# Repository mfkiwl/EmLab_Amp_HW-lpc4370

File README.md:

# EmLab Amp HW
Hardware for 80dB amp + digitizer

## Notes
- the TPS65131 regulator does some weird stuff - maybe exchange for similar AD part?

## TODO
- debug prototype

### Schematic
- nothing

### PCB
- nothing

## Links
- [BOM](https://octopart.com/bom-tool/Xo4yGKYB)
- [LPC Link 2 Schematic](https://www.nxp.com/downloads/en/schematics/LPC-Link2-SCH.pdf)
- [BGA PCB Guidelines](https://www.nxp.com/docs/en/application-note/AN10778.pdf)
- [Proper grounding #1](https://www.analog.com/en/analog-dialogue/articles/staying-well-grounded.html)
- [Proper grounding #2](https://www.maximintegrated.com/en/app-notes/index.mvp/id/5450)
- [LPC4370 Datasheet](https://www.nxp.com/docs/en/data-sheet/LPC4370.pdf)
- [W25Q80BVSSIG Datasheet](https://openwrt.org/_media/media/datasheets/flash/w25q80bv.pdf)
- [IS25LP080D-JNLA3-TR](https://cz.mouser.com/ProductDetail/ISSI/IS25LP080D-JNLA3-TR?qs=sGAEpiMZZMuIiYGg9i1FDOSOPk6CUsSSrSt5PkokTOpe%2F19c4PAU8Q%3D%3D)
- [LT3094 Datasheet](https://www.analog.com/media/en/technical-documentation/data-sheets/LT3094.pdf)
- [LT3045 Datasheet] (https://www.analog.com/media/en/technical-documentation/data-sheets/3045fa.pdf)
- [TPS7A80 Datasheet](http://www.ti.com/lit/ds/symlink/tps7a80.pdf)
- [THS4131 Datasheet](http://www.ti.com/lit/ds/symlink/ths4131.pdf)
- [LMH6518 Datasheet](http://www.ti.com/lit/ds/symlink/lmh6518.pdf)

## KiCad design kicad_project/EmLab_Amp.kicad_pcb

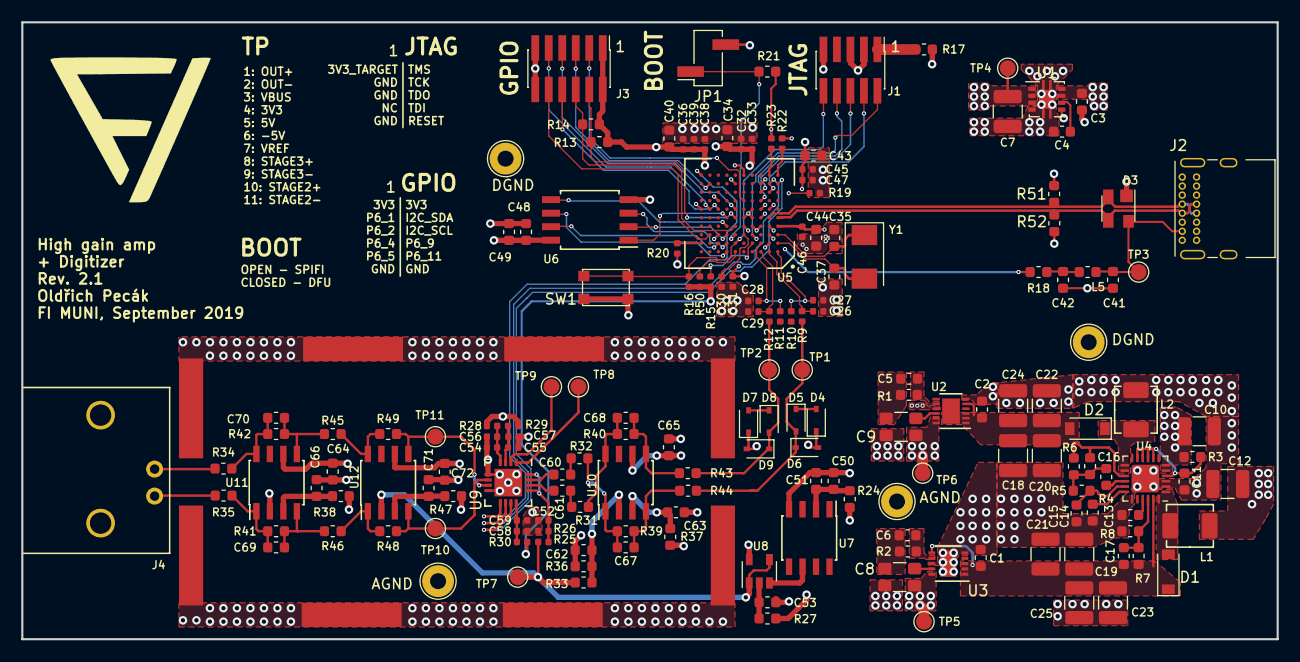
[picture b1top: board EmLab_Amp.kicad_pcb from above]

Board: 4 copper layers, 118.1 x 58.0 mm, 170 parts (0 on the bottom side), 95 nets.

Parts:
AGND: TestPoint_Loop_D2.54mm_Drill1.5mm_Beaded
AGND#2: TestPoint_Loop_D2.54mm_Drill1.5mm_Beaded
C1, C2: 470n; C_0603_1608Metric
C3: 1u; C_0603_1608Metric
C4, C13: 10n; C_0603_1608Metric
C5, C6, C14: 4u7; C_0603_1608Metric
C7, C10, C12, C18, C19, C20, C21, C22, C23, C24, C25: 4u7; C_1210_3225Metric
C8, C9: 10u; C_1210_3225Metric_SPLIT
C11, C41, C48, C51, C53, C62, C63, C64, C65, C66, C71, C72: 100n; C_0603_1608Metric
C15: 220n; C_0603_1608Metric
C16, C17: 12p; C_0603_1608Metric
C26, C27, C28, C29: 47p; C_0402_1005Metric
C30, C31, C32, C36, C39, C45, C52, C56, C57, C58: 100n; C_0402_1005Metric
C33, C38: 22n; C_0402_1005Metric
C34, C40, C43, C44, C49, C50, C60, C61: 10u; C_0603_1608Metric
C35, C37: 18p; C_0603_1608Metric
C42: 3u3; C_0603_1608Metric
C46: 3n3; C_0402_1005Metric
C47: 39n; C_0402_1005Metric
C54, C55, C59: 10n; C_0402_1005Metric
C67, C68: 69p8; C_0603_1608Metric
C69, C70: 47p; C_0603_1608Metric
D1, D2: D_Schottky; D_SOD-123
D3: PRTR5V0U2X; SOT-143
D4, D5, D6, D7, D8, D9: 1N4148WS; D_SOD-323
DGND: TestPoint_Loop_D2.54mm_Drill1.5mm_Beaded
DGND#2: TestPoint_Loop_D2.54mm_Drill1.5mm_Beaded
J1: JTAG; PinHeader_2x05_P1.27mm_Vertical_SMD
J2: USB_C_Receptacle_USB2.0; USB_C_Receptacle_GCT_USB4085
J3: GPIO_EXP; PinHeader_2x06_P1.27mm_Vertical_SMD
J4: BNC; BNC_1337543
JP1: PinHeader_1x02_P2.54mm_Vertical_SMD_Pin1Right
L1: 4u7; BOURNS-SRP4012TA
L2: 5u6; BOURNS-SRP4012TA
L5: 1R resistor; L_0603_1608Metric
R1, R2: 49K9; R_0603_1608Metric
R3, R18: 100R; R_0603_1608Metric
R4: 100K; R_0603_1608Metric
R5, R8: 130K; R_0603_1608Metric
R6: 665K; R_0603_1608Metric
R7: 536K; R_0603_1608Metric
R9, R10, R11, R12: 100R; R_0402_1005Metric
R13, R14: 4K7; R_0603_1608Metric
R15, R16, R50: 4K7; R_0402_1005Metric
R17: 0R; R_0603_1608Metric
R19: 12K1; R_0402_1005Metric
R20, R22, R23: 2K2; R_0402_1005Metric
R21: 2K2; R_0603_1608Metric
R24, R27, R37, R38, R47: 1R; R_0603_1608Metric
R25, R26: 10K; R_0402_1005Metric
R28, R29, R30: 1R; R_0402_1005Metric
R31, R32, R34, R35, R45, R46: 400R; R_0603_1608Metric
R33, R39, R40, R48, R49: 4K; R_0603_1608Metric
R36: 1K; R_0603_1608Metric
R41, R42: 40K; R_0603_1608Metric
R43, R44: 50R; R_0603_1608Metric
R51, R52: 1M; R_0603_1608Metric
SW1: RST BTN; SW_SPST_PTS810
TP1: OUT+; TestPoint_Pad_D1.5mm
TP2: OUT-; TestPoint_Pad_D1.5mm
TP3: VBUS; TestPoint_Pad_D1.5mm
TP4: 3V3; TestPoint_Pad_D1.5mm
TP5: 5V; TestPoint_Pad_D1.5mm
TP6: -5V; TestPoint_Pad_D1.5mm
TP7: V_REF; TestPoint_Pad_D1.5mm
TP8: Stage3+; TestPoint_Pad_D1.5mm
TP9: Stage3-; TestPoint_Pad_D1.5mm
TP10: Stage2+; TestPoint_Pad_D1.5mm
TP11: Stage2-; TestPoint_Pad_D1.5mm
U1: TPS7A80; TI-VSON-8
U2: LT3094xDD; DFN-12-1EP_3x3mm_P0.45mm_EP1.66x2.38mm
U3: LT3045xDD; DFN-10-1EP_3x3mm_P0.5mm_EP1.55x2.48mm
U4: TPS6513x; QFN-24-1EP_4x4mm_P0.5mm_EP2.6x2.6mm
U5: LPC4370-TFBGA100; BGA-100_10x10_10.0x10.0mm
U6: IS25LP080D; SOIJ-8_5.3x5.3mm_P1.27mm
U7: ADR421; SOIC-8_3.9x4.9mm_P1.27mm
U8: MCP601R; SOT-23-5
U9: LMH6518; QFN-16-1EP_4x4mm_P0.5mm_EP2.6x2.6mm
U10, U11, U12: THS4131ID; SOIC-8_3.9x4.9mm_P1.27mm
Y1: 12MHz Crystal; Crystal_SMD_Abracon_ABM3-2Pin_5.0x3.2mm

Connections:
+3V3: C7.1, C31.1, C32.1, C33.1, C34.1, C36.1, C38.1, C39.1, C40.1, C43.1, C44.1, C45.1, C46.1, C47.1, C48.1, C49.1, J3.1, J3.2, R13.1, R14.1, R15.1, R16.1, R17.2, R21.1, R23.1, R30.1, R50.1, TP4.1, U1.1, U1.2, U1.3, U5.B2, U5.D1, U5.D2, U5.E4, U5.E5, U5.F4, U5.F10, U5.K5, U6.8
+5V: C8.2, R24.1, R27.1, R28.1, R29.1, R37.1, R38.1, R47.1, TP5.1, U3.9, U3.10
-5V: C9.2, C65.2, C66.2, C72.2, TP6.1, U2.10, U2.11, U2.12, U10.6, U11.6, U12.6
/Amplifier/S3_CS: U5.K10, U9.9
/Amplifier/S3_DIO: U5.J2, U9.10
/Amplifier/S3_SCLK: U5.J1, U9.11
/Amplifier/STAGE2_NEG: R49.2, TP11.1, U9.7, U12.5
/Amplifier/STAGE2_POS: R48.1, TP10.1, U9.6, U12.4
/Amplifier/V_REF: R25.1, R33.1, TP7.1, U8.1, U8.4, U12.2
/LPC4370-GPIO/BOOT_0: R23.2, U5.K2
/LPC4370-GPIO/BOOT_1: R22.1, U5.K1
/LPC4370-GPIO/BOOT_2: JP1.1, R21.2, U5.C6
/LPC4370-GPIO/BOOT_3: R20.1, U5.B10
/LPC4370-GPIO/GPIO_0: J3.3, U5.G5
/LPC4370-GPIO/GPIO_1: J3.5, U5.J9
/LPC4370-GPIO/GPIO_2: J3.7, U5.F6
/LPC4370-GPIO/GPIO_3: J3.9, U5.F9
/LPC4370-GPIO/GPIO_4: J3.8, U5.F8
/LPC4370-GPIO/GPIO_5: J3.10, U5.C9
/LPC4370-GPIO/I2C_SCL: J3.6, R14.2, U5.D6
/LPC4370-GPIO/I2C_SDA: J3.4, R13.2, U5.E6
/LPC4370-GPIO/SPIFI_CS: U5.E7, U6.1
/LPC4370-GPIO/SPIFI_MISO: U5.C7, U6.2
/LPC4370-GPIO/SPIFI_MOSI: U5.D7, U6.5
/LPC4370-GPIO/SPIFI_SCK: U5.A7, U6.6
/LPC4370-GPIO/SPIFI_SIO2: U5.B7, U6.3
/LPC4370-GPIO/SPIFI_SIO3: U5.B8, U6.7
/LPC4370-JTAG-PWR-MISC/ADC0: D5.2, D6.1, R9.2, R44.2, TP1.1
/LPC4370-JTAG-PWR-MISC/ADC3: D8.2, D9.1, R12.2, R43.1, TP2.1
/LPC4370-JTAG-PWR-MISC/DBGEN: R50.2, U5.A6
/LPC4370-JTAG-PWR-MISC/RESET: J1.10, R16.2, SW1.1, U5.B6
/LPC4370-JTAG-PWR-MISC/TCK: J1.4, U5.H2
/LPC4370-JTAG-PWR-MISC/TDI: J1.8, U5.G3
/LPC4370-JTAG-PWR-MISC/TDO: J1.6, U5.H3
/LPC4370-JTAG-PWR-MISC/TMS: J1.2, U5.C4
/LPC4370-JTAG-PWR-MISC/TRST: R15.2, U5.B4
/LPC4370-USB/USB_VBUS: C3.1, C10.1, C12.1, C41.1, D3.4, J2.A4, J2.A9, J2.B4, J2.B9, L1.1, L5.2, R3.2, TP3.1, U1.5, U1.7, U1.8, U4.5, U4.6
/Power/VNEG: C2.2, C16.2, C18.1, C20.1, C22.1, C24.1, D2.2, R6.2, U2.1, U2.2, U2.3, U2.5, U2.13, U4.15
/Power/VPOS: C1.2, C17.1, C19.1, C21.1, C23.1, C25.1, D1.1, R7.1, U3.1, U3.2, U3.3, U3.6, U4.23
GND: AGND.1, AGND#2.1, C1.1, C2.1, C3.2, C4.2, C5.1, C6.1, C7.2, C8.1, C9.1, C10.2, C11.2, C12.2, C13.2, C14.2, C15.2, C18.2, C19.2, C20.2, C21.2, C22.2, C23.2, C24.2, C25.2, C26.2, C27.2, C28.2, C29.2, C30.2, C31.2, C32.2, C33.2, C34.2, C35.2, C36.2, C37.2, C38.2, C39.2, C40.2, C41.2, C42.2, C43.2, C44.2, C45.2, C46.2, C47.2, C48.2, C49.2, C50.1, C51.1, C52.1, C53.1, C54.1, C55.1, C56.1, C57.1, C58.1, C59.1, C62.1, C63.1, C64.1, C65.1, C66.1, C71.1, C72.1, D3.1, D4.1, D6.2, D7.1, D9.2, DGND.1, DGND#2.1, J1.3, J1.5, J1.9, J2.A1, J2.A12, J2.B1, J2.B12, J2.S1, J3.11, J3.12, J4.2, JP1.2, L2.2, R1.1, R2.1, R8.2, R19.2, R20.2, R22.2, R26.1, R35.1, R36.1, R51.2, R52.2, SW1.2, U1.4, U1.9, U2.6, U2.9, U3.5, U3.8, U3.11, U4.2, U4.3, U4.19, U4.25, U5.C2, U5.C8, U5.D3, U5.D4, U5.D5, U5.F2, U5.G8, U5.J3, U5.J6, U6.4, U7.4, U8.5, U9.5, U9.8, U9.17, U11.2
unnamed: C4.1, U1.6
unnamed: C5.2, R1.2, U2.8
unnamed: C6.2, R2.2, U3.7
unnamed: C11.1, R3.1, U4.4, U4.8, U4.9, U4.10, U4.11
unnamed: C13.1, U4.21
unnamed: C14.1, U4.18
unnamed: C15.1, R5.1, U4.17
unnamed: C16.1, R4.1, R5.2, R6.1
unnamed: C17.2, R7.2, R8.1, U4.22
unnamed: C26.1, R9.1, U5.A2
unnamed: C27.1, R10.1, U5.A1
unnamed: C28.1, R11.1, U5.B3
unnamed: C29.1, R12.1, U5.A3
unnamed: C30.1, U5.C5
unnamed: C35.1, U5.C1, Y1.1
unnamed: C37.1, U5.B1, Y1.2
unnamed: C42.1, L5.1, R18.2
unnamed: C50.2, C51.2, R24.2, U7.2
unnamed: C52.2, R25.2, R26.2, U9.13, U9.16
unnamed: C53.2, R27.2, U8.2
unnamed: C54.2, C56.2, R28.2, U9.4
unnamed: C55.2, C57.2, R29.2, U9.3
unnamed: C58.2, C59.2, R30.2, U9.12
unnamed: C60.1, U9.15
unnamed: C60.2, R32.1
unnamed: C61.1, U9.14
unnamed: C61.2, R31.2
unnamed: C62.2, R33.2, R36.2, U10.2
unnamed: C63.2, R37.2, U10.3
unnamed: C64.2, R38.2, U11.3
unnamed: C67.1, R39.2, R44.1, U10.4
unnamed: C67.2, R32.2, R39.1, U10.1
unnamed: C68.1, R40.2, R43.2, U10.5
unnamed: C68.2, R31.1, R40.1, U10.8
unnamed: C69.1, R41.2, R46.1, U11.4
unnamed: C69.2, R35.2, R41.1, U11.1
unnamed: C70.1, R42.2, R45.2, U11.5
unnamed: C70.2, R34.1, R42.1, U11.8
unnamed: C71.2, R47.2, U12.3
unnamed: D1.2, L1.2, U4.1, U4.24
unnamed: D2.1, L2.1, U4.13, U4.14
unnamed: D3.2, J2.A7, J2.B7, R51.1, U5.E2
unnamed: D3.3, J2.A6, J2.B6, R52.1, U5.E1
unnamed: D4.2, D5.1
unnamed: D7.2, D8.1
unnamed: J1.1, R17.1
unnamed: J4.1, R34.2
unnamed: R4.2, U4.16
unnamed: R18.1, U5.E3
unnamed: R19.1, U5.F3
unnamed: R45.1, R49.1, U12.8
unnamed: R46.2, R48.2, U12.1
unnamed: TP8.1, U9.1
unnamed: TP9.1, U9.2
unnamed: U7.6, U8.3

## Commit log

2019-03-12 add gerber and drill files to .gitignore
2019-03-13 Add kicad project
2019-03-13 notes
2019-03-27 LPC4370 misc, jtag, power
2019-03-27 add USB interface
2019-04-01 add LPC4370 gpio
2019-04-03 Add power supplies
2019-04-15 Amplifier stage 1 and 2
2019-04-17 Amplifier stage 3&4, v_ref
2019-04-17 Schematic done, Rev1
2019-05-08 Start on PCB
2019-05-08 PCB: Amplifier done, digital done
2019-05-08 edit readme
2019-05-09 PCB: finished analog and digital
2019-05-10 PCB layout done
2019-05-13 PCB rev. 1 done
2019-05-20 PCB - add GND test points
2019-05-24 manufacturing files
2019-05-28 readme + interactive bom
2019-05-28 add image
2019-07-12 Change USB connector
2019-07-12 cleanup
2019-07-12 cleanup 2
2019-07-25 add BOM
2019-09-10 add .gitattributes
2019-09-10 wolololo
2019-09-23 Rev 2
2019-09-23 iBom + formatting PCB
2019-09-23 new gerbers
2019-10-11 rev 2.1
